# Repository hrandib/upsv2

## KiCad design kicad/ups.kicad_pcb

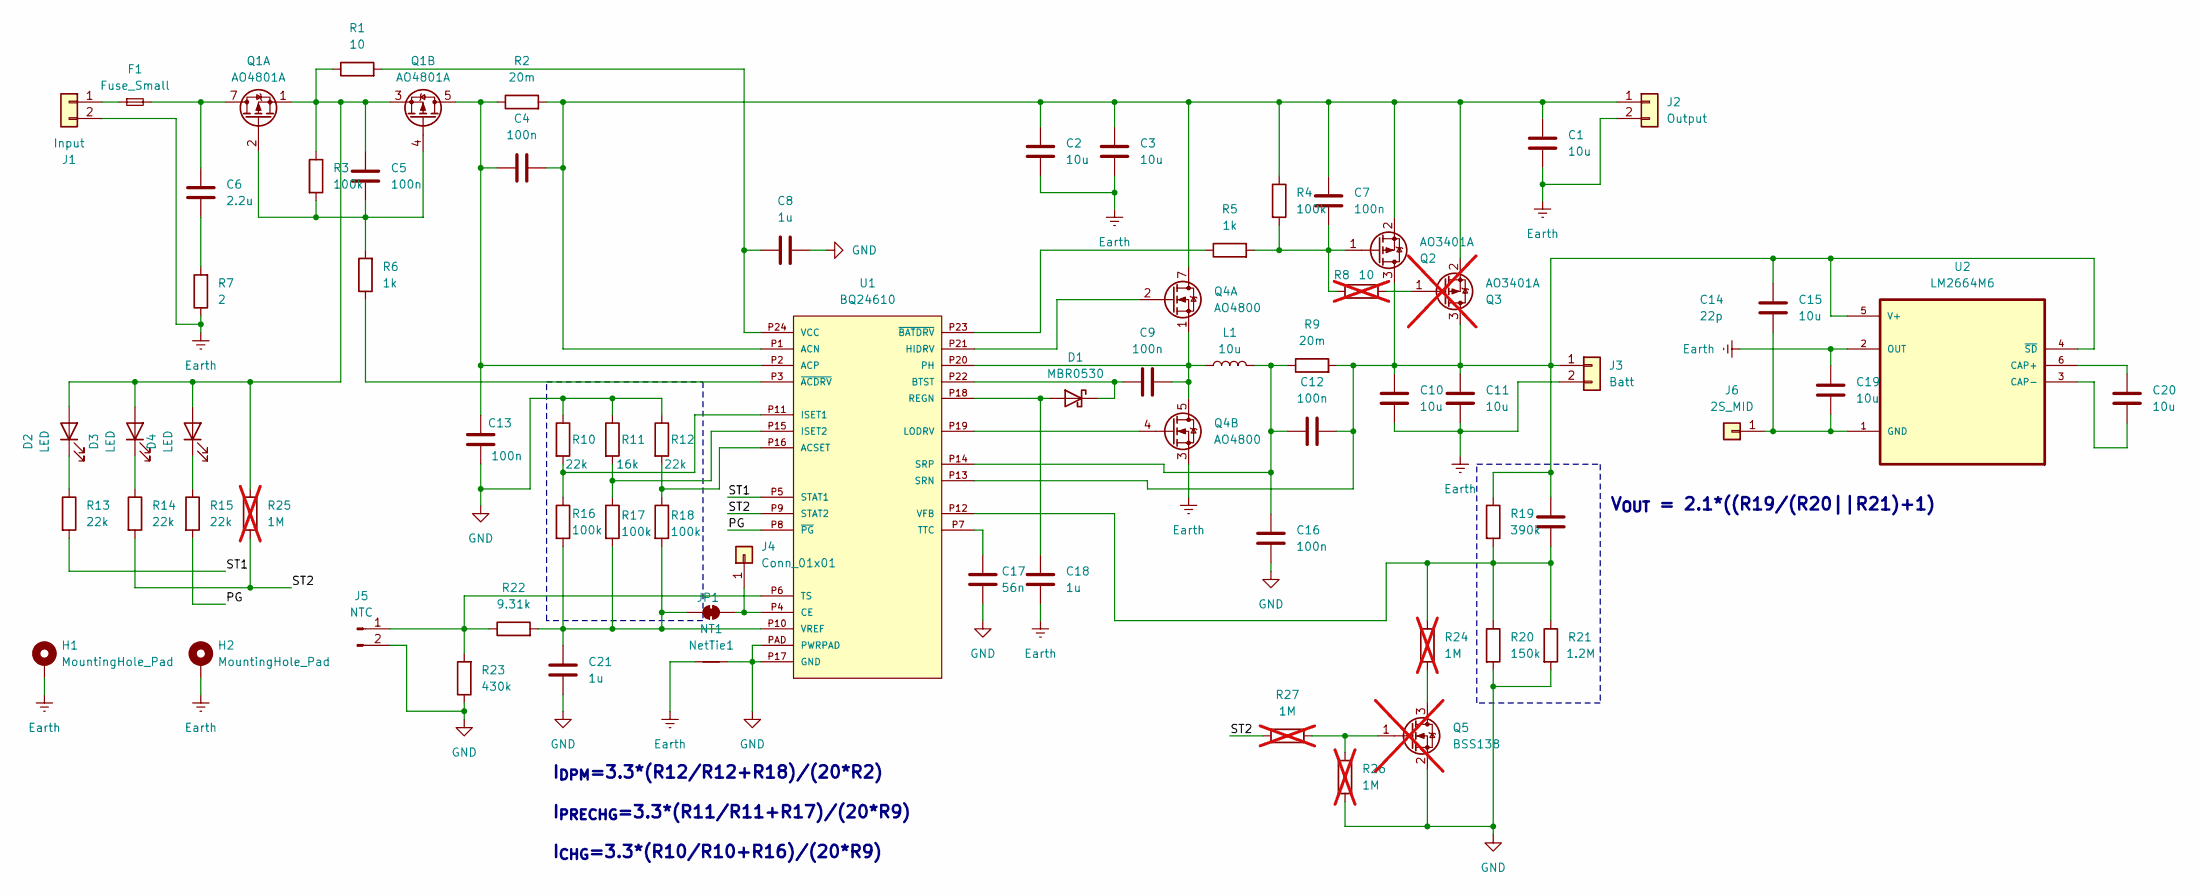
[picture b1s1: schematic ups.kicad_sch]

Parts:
C1, C2, C3, C10, C11, C15, C19, C20: 10u; C_1206_3216Metric
C4, C5, C7, C9, C12, C13, C16: 100n; C_0603_1608Metric
C6: 2.2u; C_0805_2012Metric
C8, C18: 1u; C_0805_2012Metric
C14: 22p; C_0603_1608Metric
C17: 56n; C_0603_1608Metric
C21: 1u; C_0603_1608Metric
D1: MBR0530; D_SOD-323F
D2, D3, D4: LED; LED_0805_2012Metric
F1: Fuse_Small; Fuse_1812_4532Metric
H1, H2: MountingHole_Pad; MountingHole_3.2mm_M3_DIN965_Pad
J1: Input; SolderWire-1.5sqmm_1x02_P7.8mm_D1.7mm_OD3.9mm
J2: Output; SolderWire-1.5sqmm_1x02_P7.8mm_D1.7mm_OD3.9mm
J3: Batt; SolderWire-1.5sqmm_1x02_P7.8mm_D1.7mm_OD3.9mm
J4: Conn_01x01; SolderWire-0.75sqmm_1x01_D1.25mm_OD3.5mm
J5: NTC; PinHeader_1x02_P2.54mm_Vertical
J6: 2S_MID; SolderWire-0.75sqmm_1x01_D1.25mm_OD3.5mm
JP1: SolderJumper_2_Bridged; SolderJumper-2_P1.3mm_Bridged_RoundedPad1.0x1.5mm
L1: 10u; L_Abracon_ASPI-0630LR
NT1: NetTie1; NetTie-2_SMD_Pad2.0mm
Q1: AO4801A; SOIC-8_3.9x4.9mm_P1.27mm
Q2: AO3401A; SOT-23
Q3: AO3401A; SOT-23; not fitted
Q4: AO4800; SOIC-8_3.9x4.9mm_P1.27mm
Q5: BSS138; SOT-23; not fitted
R1: 10; R_0603_1608Metric
R2, R9: 20m; R_1206_3216Metric
R3, R4: 100k; R_0603_1608Metric
R5, R6: 1k; R_0603_1608Metric
R7: 2; R_1206_3216Metric
R8: 10; R_0603_1608Metric; not fitted
R10, R12: 22k; R_0805_2012Metric_Pad1.20x1.40mm_HandSolder
R11: 16k; R_0805_2012Metric_Pad1.20x1.40mm_HandSolder
R13, R14, R15: 22k; R_0603_1608Metric
R16, R17, R18: 100k; R_0805_2012Metric_Pad1.20x1.40mm_HandSolder
R19: 390k; R_0805_2012Metric_Pad1.20x1.40mm_HandSolder
R20: 150k; R_0805_2012Metric_Pad1.20x1.40mm_HandSolder
R21: 1.2M; R_0805_2012Metric_Pad1.20x1.40mm_HandSolder
R22: 9.31k; R_0603_1608Metric
R23: 430k; R_0603_1608Metric
R24: 1M; R_0805_2012Metric_Pad1.20x1.40mm_HandSolder; not fitted
R25, R26, R27: 1M; R_0603_1608Metric; not fitted
U1: BQ24610; VQFN24_TI
U2: LM2664M6; TSOT-23-6_HandSoldering

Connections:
/PG: R15.2, U1.P8 (~PG)
/ST1: R13.2, U1.P5 (STAT1)
/ST2: R14.2, R25.2, R27.1, U1.P9 (STAT2)
Earth: C1.2, C2.2, C3.2, C10.2, C11.2, C18.2, C19.1, H1.1, H2.1, J1.2, J2.2, J3.2, NT1.2, Q4.3 (S2), R7.1, U2.2 (OUT)
GND: C8.2, C13.1, C16.1, C17.2, C21.2, J5.2, NT1.1, Q5.2 (S), R10.1, R11.1, R12.1, R20.2, R21.2, R23.1, R26.2, U1.P17 (GND), U1.PAD (PWRPAD)
unnamed: C6.1, F1.2, Q1.7 (D1), Q1.8 (D1)
unnamed: C6.2, R7.2
unnamed: C18.1, D1.2 (A), U1.P18 (REGN)
unnamed: C9.1, D1.1 (K), U1.P22 (BTST)
unnamed: C5.1, D2.2 (A), D3.2 (A), D4.2 (A), Q1.1 (S1), Q1.3 (S2), R1.1, R3.1, R25.1
unnamed: D2.1 (K), R13.1
unnamed: D3.1 (K), R14.1
unnamed: D4.1 (K), R15.1
unnamed: F1.1, J1.1
unnamed: C1.1, C2.1, C3.1, C4.2, C7.1, J2.1, Q2.2 (S), Q3.2 (S), Q4.7 (D1), Q4.8 (D1), R2.2, R4.1, U1.P1 (ACN)
unnamed: C10.1, C11.1, C12.2, C14.1, C15.1, J3.1, Q2.3 (D), Q3.3 (D), R9.2, R19.1, U1.P13 (SRN), U2.4 (~SD), U2.5 (V+)
unnamed: J4.1, JP1.2 (B), U1.P4 (CE)
unnamed: J5.1, R22.1, R23.2, U1.P6 (TS)
unnamed: C15.2, C19.2, J6.1, U2.1 (GND)
unnamed: C21.1, JP1.1 (A), R16.2, R17.2, R18.2, R22.2, U1.P10 (VREF)
unnamed: C5.2, Q1.2 (G1), Q1.4 (G2), R3.2, R6.2
unnamed: C7.2, Q2.1 (G), R4.2, R5.2, R8.1
unnamed: Q3.1 (G), R8.2
unnamed: Q4.2 (G1), U1.P21 (HIDRV)
unnamed: C9.2, L1.1, Q4.1 (S1), Q4.5 (D2), Q4.6 (D2), U1.P20 (PH)
unnamed: Q4.4 (G2), U1.P19 (LODRV)
unnamed: Q5.3 (D), R24.2
unnamed: Q5.1 (G), R26.1, R27.2
unnamed: C4.1, C13.2, Q1.5 (D2), Q1.6 (D2), R2.1, U1.P2 (ACP)
unnamed: R12.2, R18.1, U1.P16 (ACSET)
unnamed: R10.2, R16.1, U1.P11 (ISET1)
unnamed: R11.2, R17.1, U1.P15 (ISET2)
unnamed: C12.1, C16.2, L1.2, R9.1, U1.P14 (SRP)
unnamed: C17.1, U1.P7 (TTC)
unnamed: C8.1, R1.2, U1.P24 (VCC)
unnamed: C14.2, R19.2, R20.1, R21.1, R24.1, U1.P12 (VFB)
unnamed: R6.1, U1.P3 (~ACDRV)
unnamed: R5.1, U1.P23 (~BATDRV)
unnamed: C20.1, U2.6 (CAP+)
unnamed: C20.2, U2.3 (CAP-)

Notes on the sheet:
V_{OUT} = 2.1*((R19/(R20||R21)+1)
I_{DPM}=3.3*(R12/R12+R18)/(20*R2) I_{PRECHG}=3.3*(R11/R11+R17)/(20*R9) I_{CHG}=3.3*(R10/R10+R16)/(20*R9)

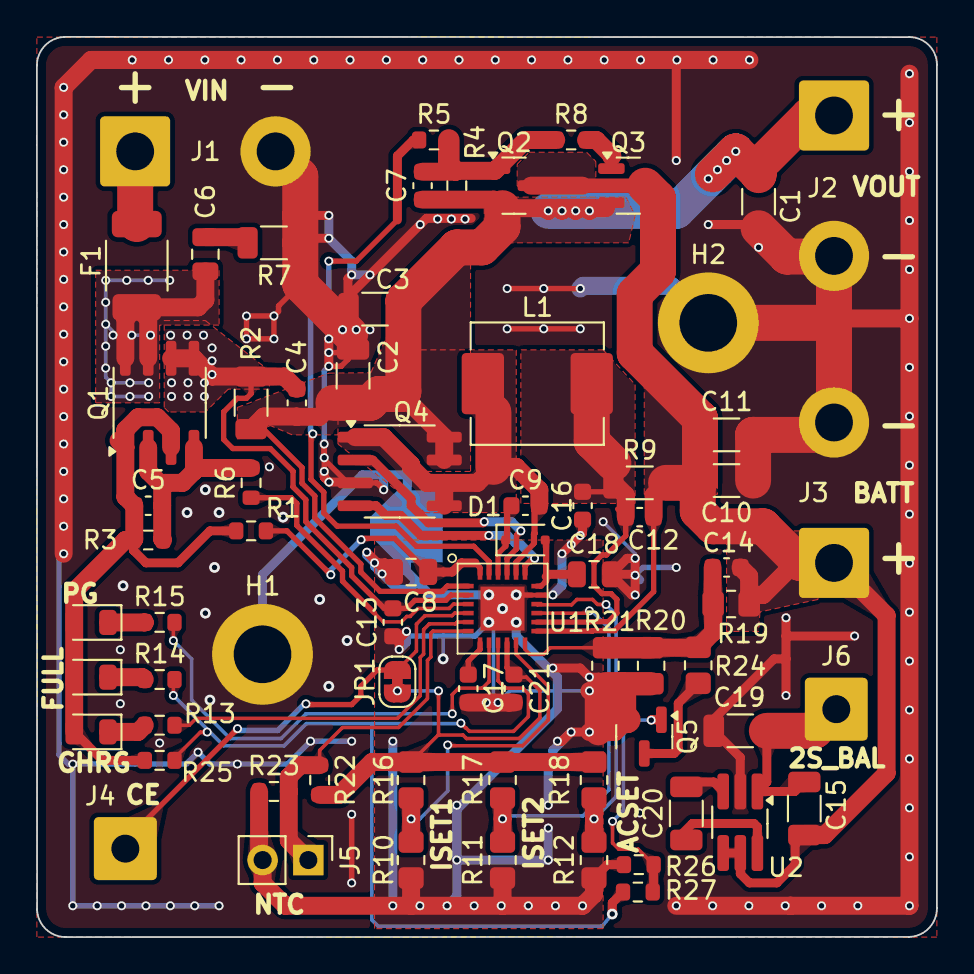
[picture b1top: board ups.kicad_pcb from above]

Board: 2 copper layers, 50.0 x 50.0 mm, 71 parts (1 on the bottom side), 40 nets.

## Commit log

2024-05-27 Add schematics
2024-05-28 Add PCB and Gerbers
2024-05-28 Minor pcb fix
2024-05-28 Add ACSET ISETx labels to silkscreen
2024-05-28 Minor pcb rerouting
2024-05-28 Cleanup ground polygon islands
2024-06-01 Add recharge threshold control
2024-06-01 Minor reroute
2024-06-02 More copper for the input mosfet
2024-06-22 Update part names, minor fix in the ground plane
2024-06-22 misc: Add alternative parts datasheets
2024-06-22 pcb: Add interactive BOM
2024-06-22 pcb: Update part names
2024-06-22 Add equation formulas to schematics
2024-06-22 Remove outdated Gerber files
2024-06-22 Update iBOM
2024-06-23 sch: Fix precharge equation
